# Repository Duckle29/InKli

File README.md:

# InKli

From the Danish "Indeklima" or "indoor climate", is an small sensor box, measuring CO2, temperature and relative humidity.

It displays this on an E-paper display, to allow you to keep an eye on the air in the room you're in.  
Additionally, as it is made with ESPHome, it can also easily connect to a Homeassistant instance, for further home automation and logging.

## History
Quite some time ago I built an air quality monitor, and played around with it. (https://blog.mikkel.cc/posts/airq/) It had PM10 sensors, CO2 sensors and BME680 for TVOC.

I've since had this running, and while it was fine, it was bulky, and I only ever really paid attention to the temperature, humidity and CO2 sensors.
The display I used on that box also had issues. Mainly with the backlight being a significant heat source, and an annoyance at night.

So now this is the replacement.
It has:
- ESP32
- 2.13" Waveshare E-paper display  (https://www.waveshare.com/2.13inch-e-paper.htm)
- IR remote demodulator
- 2 side-firing high-current IR LEDs 
- QWIIC port for future expansion / experimentation
- Single push button
- Touch-pad under screen (tested, works so~so, not great)
It also has a (hopefully) quite efficient 3V3 buck regulator to reduce self heating. (pretty good, seems around 2-3C self heating enclosed, mostly from the ESP itself )

At this point, I have the displays and the sensors. I'm getting most things working first, so I don't learn I've used a strapping pin when I have PCBs in hand and they don't cooperate.
I'm pretty happy with the simple display layout, and will see tomorrow how the graph turns out (set to 8h)

The IR blasters are there because one of these sensors will pull double duty, and act as an IR remote for a heat pump. 
On the rest of the PCBs these probably won't be populated.

## Firmware

There are two variants, both in `esphome/`:

- `inkli.yaml`: the device itself (CO2, temperature and humidity on the e-paper display, Home Assistant, Wi-Fi setup). This is the one for boards without the IR LED fitted.
- `inkli-heatpump.yaml`: the same, plus Panasonic heat pump control over the IR LED. It includes `inkli.yaml` and adds `heatpump.yaml`.

Each release has both: `inkli-esp32.*` and `inkli-heatpump-esp32.*`. A device updates itself (hold the button for 6 s) from the file with its own name on the OTA server.

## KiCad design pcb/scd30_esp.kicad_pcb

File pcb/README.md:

# SCD30 ESP32 backback

This is a small PCB combining an ESP32 WROOM module with an SCD30. It's intended to be USB powered, and has the option to mount a CH340C if you want on-board USB<>serial.

It's intended for use with ESPHome or similar.

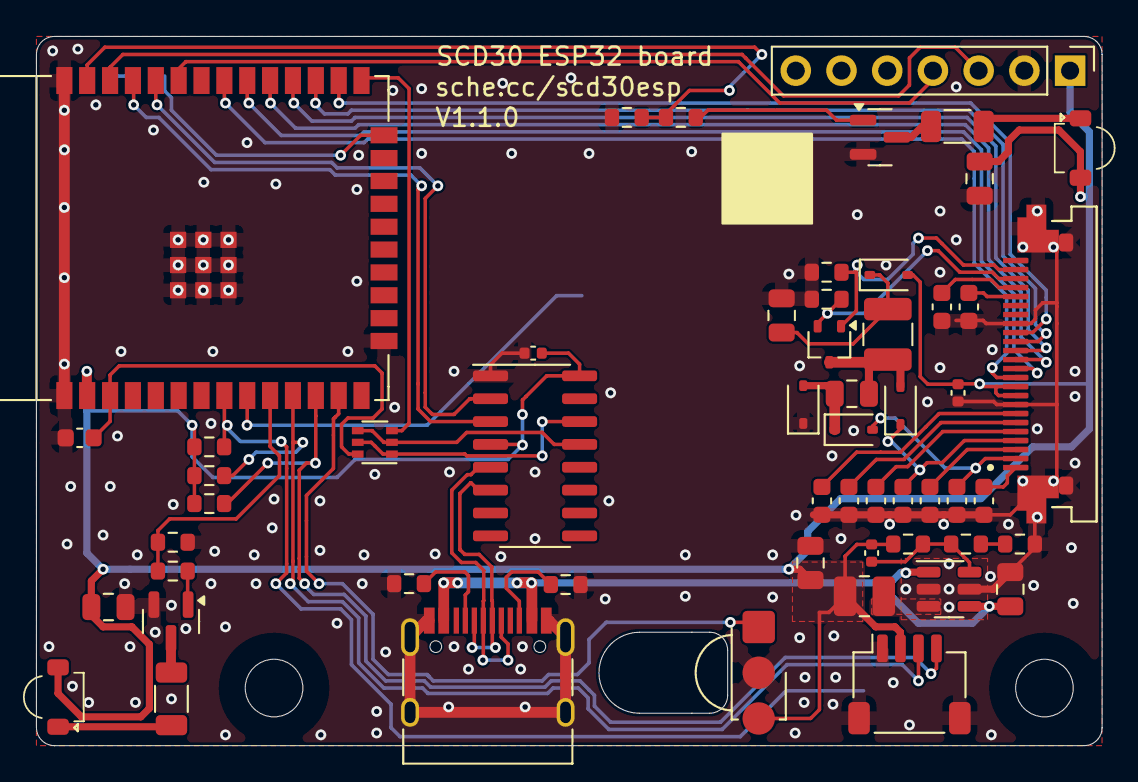
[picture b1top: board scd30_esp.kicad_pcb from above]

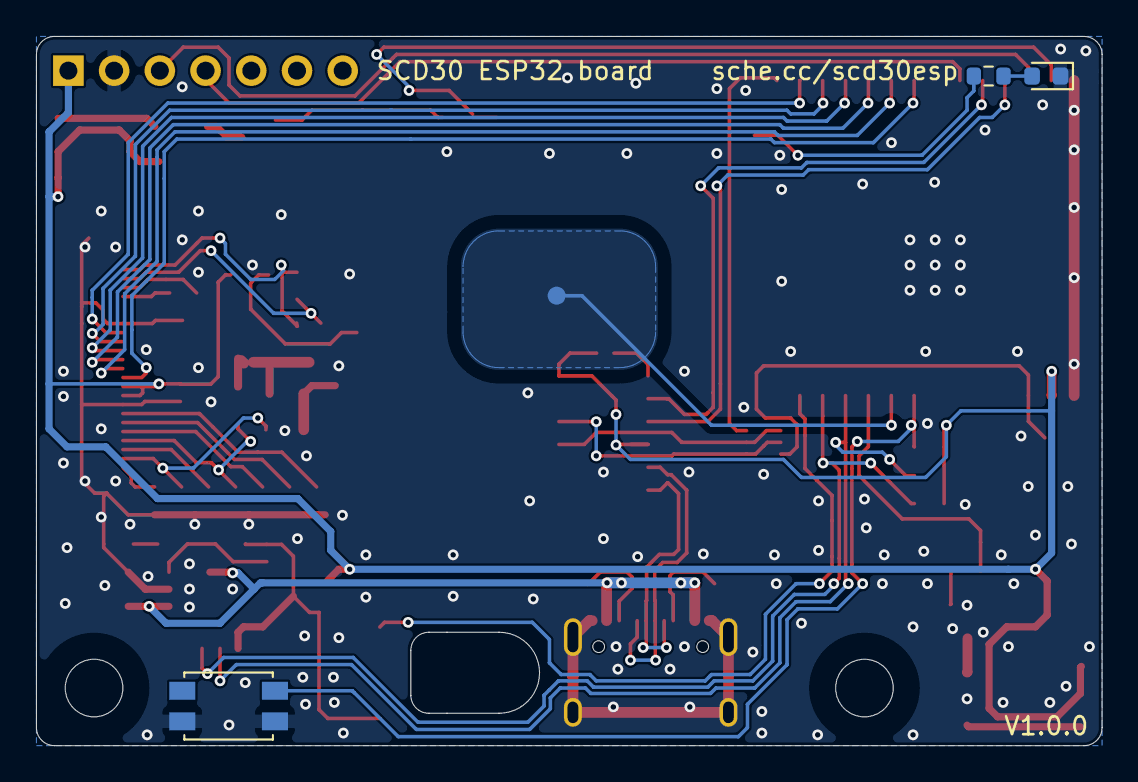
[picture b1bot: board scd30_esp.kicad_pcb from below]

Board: 2 copper layers, 59.2 x 39.4 mm, 59 parts (4 on the bottom side), 53 nets.

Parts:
C1: 120pF; C_0402_1005Metric
C2, C6, C7: 22uF; C_0805_2012Metric
C3: 4.7uF; C_0805_2012Metric
C4, C20: 0.1uF; C_0402_1005Metric
C5, C10, C11, C12, C13, C14, C15, C16, C17, C18: 1uF; C_0603_1608Metric
C8, C9: 4u7; C_0805_2012Metric
D1, D2, D3, D4: NSR0530HT1G; D_SOD-323
D5, D6: LED_Small; LED_Vishay_VSMB2943SL
D7: LED_Small; LED_0603_1608Metric
J1: SCD30; PinHeader_1x07_P2.54mm_Vertical
J2: USB_C_Receptacle_USB2.0; USB_C_Receptacle_HRO_TYPE-C-31-M-12
J3: 24P P0.5mm waveshare E-paper display; AMPHENOL_SFV24R-4STE1HLF
J4: QWIIC; JST_SH_SM04B-SRSS-TB_1x04-1MP_P1.00mm_Horizontal
L1: 1uH; L_1008_2520Metric
L2: 68uF; L_1210_3225Metric
Q1: Si1308EDL; SOT-323_SC-70
Q2, Q4: Q_NMOS_GSD; SOT-23
Q3: BSS138PS; SOT-363_SC-70-6
R1: 82k; R_0603_1608Metric
R2: 8k2; R_0603_1608Metric
R3, R7, R10, R13, R14: 10k; R_0603_1608Metric
R4, R5: 5k1; R_0603_1608Metric
R6: 3R; R_0603_1608Metric
R8, R9, R12, R15: 2k2; R_0603_1608Metric
R11, R16: 3R; R_1206_3216Metric
R17: 1k; R_0603_1608Metric
SW1: SW_SPST; SW_SPST_EVQP2
TP1: Touch TP; TestPoint_Pad_D1.0mm
U1: TPS62A01PDDCR; SOT-23-6
U2: ESP32-WROOM-E; ESP32-WROOM-32E
U3: CH340C; SOIC-16_3.9x9.9mm_P1.27mm
U4: TSOP38G36; Vishay_MINICAST-3Pin

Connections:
+3V3: C1.1, C2.1, C4.1, C6.1, C7.1, C20.1, D1.2 (A), D5.2 (A), D6.2 (A), J1.1, J3.9, J3.10, J4.2, L1.2, R1.1, R8.1, R9.1, R10.1, U2.2 (3V3), U3.4 (V3), U3.16 (VCC), U4.3 (Vs)
/BTN: R10.2, SW1.1 (A), U2.8 (32K_XP/GPIO32/ADC1_CH4)
/D+: J2.A6 (D+), J2.B6 (D+), U3.5 (UD+)
/D-: J2.A7 (D-), J2.B7 (D-), U3.6 (UD-)
/DISP_BUSY: J3.16, U2.26 (ADC2_CH0/GPIO4)
/DISP_SDA: J3.11, U2.31 (GPIO19)
/ESP_EN: C5.1, Q3.6 (D), U2.3 (EN/CHIP_PU)
/ESP_IO0: Q3.3 (D), U2.25 (GPIO0/BOOT/ADC2_CH1)
/IR_RX: U2.13 (MTMS/GPIO14/ADC2_CH6), U4.1 (OUT)
/IR_TX_L: R12.1, R13.1, U2.37 (GPIO23)
/IR_TX_R: R14.1, R15.1, U2.10 (DAC_1/ADC2_CH8/GPIO25)
/MCU_RX+: U2.34 (U0RXD/GPIO3), U3.2 (TXD)
/MCU_TX-: U2.35 (U0TXD/GPIO1), U3.3 (RXD)
/QWIIC_SCL: J4.4, R9.2, U2.12 (ADC2_CH7/GPIO27)
/QWIIC_SDA: J4.3, R8.2, U2.11 (DAC_2/ADC2_CH9/GPIO26)
/SCL: J1.3, U2.36 (GPIO22)
/SCLK: J3.12, U2.30 (GPIO18)
/SDA: J1.4, U2.33 (GPIO21)
/TOUCH: TP1.1 (1_1), U2.9 (32K_XN/GPIO33/ADC1_CH5)
/Waveshare E-ink/GDR: J3.23, Q1.1 (G), R7.1
/Waveshare E-ink/RESE: J3.22, Q1.2 (S), R6.1
/Waveshare E-ink/VCOM: C10.1, J3.1
/Waveshare E-ink/VGH: C13.1, D4.1 (K), J3.4
/Waveshare E-ink/VGL: C11.1, D3.2 (A), J3.2
/Waveshare E-ink/VPP: C15.1, J3.6
/Waveshare E-ink/VSH1: C14.1, J3.5
/Waveshare E-ink/VSH2: C17.1, J3.20
/Waveshare E-ink/VSL: C12.1, J3.3
/Waveshare E-ink/V_CORE: C16.1, J3.7
/status_led: R17.2, U2.24 (ADC2_CH2/GPIO2)
/~DISP_CS: J3.13, U2.29 (GPIO5)
/~DISP_D/C: J3.14, U2.28 (GPIO17)
/~DISP_RST: J3.15, U2.27 (GPIO16)
GND: C2.2, C3.2, C4.2, C5.2, C6.2, C7.2, C9.2, C10.2, C11.2, C12.2, C13.2, C14.2, C15.2, C16.2, C17.2, C18.2, C20.2, D2.1 (K), D7.1 (K), J1.2, J2.A1 (GND), J2.A12 (GND), J2.B1 (GND), J2.B12 (GND), J2.S1 (SHIELD), J3.8, J3.17, J3.MP (MountPin), J4.1, J4.MP (MountPin), Q2.2 (S), Q4.2 (S), R3.2, R4.2, R5.2, R6.2, R7.2, R13.2, R14.2, SW1.2 (B), U1.2 (GND), U1.5 (PG), U2.1 (GND), U2.15 (GND), U2.38 (GND), U2.39 (GND_THERMAL), U3.1 (GND), U4.2 (GND)
unnamed: C9.1, D1.1 (K), L2.1
unnamed: C8.2, D2.2 (A), D3.1 (K)
unnamed: C8.1, D4.2 (A), L2.2, Q1.3 (D)
unnamed: D5.1 (K), R11.1
unnamed: D6.1 (K), R16.1
unnamed: D7.2 (A), R17.1
unnamed: J2.A5 (CC1), R5.1
unnamed: J2.B5 (CC2), R4.1
unnamed: C18.1, J3.21
unnamed: Q2.3 (D), R11.2
unnamed: Q2.1 (G), R12.2
unnamed: Q3.2 (G), Q3.4 (S), U3.13 (~DTR)
unnamed: Q3.1 (S), Q3.5 (G), U3.14 (~RTS)
unnamed: Q4.3 (D), R16.2
unnamed: Q4.1 (G), R15.2
unnamed: R2.2, R3.1
unnamed: C1.2, R1.2, R2.1, U1.6 (FB)
unnamed: L1.1, U1.3 (SW)
VBUS: C3.1, J2.A4 (VBUS), J2.A9 (VBUS), J2.B4 (VBUS), J2.B9 (VBUS), U1.1 (EN), U1.4 (VIN)

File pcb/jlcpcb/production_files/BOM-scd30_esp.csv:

Comment,Designator,Footprint,LCSC,Quantity
120pF,C1,C_0402_1005Metric,C106996,1
0.1uF,"C20,C4",C_0402_1005Metric,C1525,2
1uF,"C10,C11,C12,C13,C14,C15,C16,C17,C5,C8,C9",C_0603_1608Metric,C15849,11
USB_C_Receptacle_USB2.0,J2,USB_C_Receptacle_HRO_TYPE-C-31-M-12,C165948,1
BSS138PS,Q3,SOT-363_SC-70-6,C193381,1
4.7uF,C3,C_0805_2012Metric,C19666,1
68uF,L2,L_1210_3225Metric,C223228,1
TPS62A01PDDCR,U1,SOT-23-6,C22445521,1
LED_Small,D7,LED_0603_1608Metric,C2286,1
360k,R2,R_0603_1608Metric,C23146,1
82k,R1,R_0603_1608Metric,C23254,1
10k,"R10,R13,R14,R17,R3,R7",R_0603_1608Metric,C25804,6
1uH,L1,L_1008_2520Metric,C435392,1
22uF,"C2,C6,C7",C_0805_2012Metric,C45783,3
Si1308EDL,Q1,SOT-323_SC-70,C469327,1
SW_SPST,SW1,SW_SPST_EVQP2,C512395,1
24P P0.5mm waveshare E-paper display,J3,AMPHENOL_SFV24R-4STE1HLF,C5343283,1
NSR0530HT1G,"D1,D2,D3,D4",D_SOD-323,C556393,4
2k2,"R12,R15,R4,R5,R8,R9",R_0603_1608Metric,C6119849,6
ESP32-WROOM-E,U2,ESP32-WROOM-32E,C701342,1
CH340C,U3,SOIC-16_3.9x9.9mm_P1.27mm,C7464026,1
3R,R6,R_0603_1608Metric,,1
TSOP38G36,U4,Vishay_MINICAST-3Pin,,1

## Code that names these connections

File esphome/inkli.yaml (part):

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  - platform: gpio
    id: btn
    pin:
      number: GPIO32
      inverted: True
      #allow_other_uses: True
      mode:
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                - display.page.show: page_co2_graph

  # - platform: esp32_touch
  #   pin: GPIO33
  #   threshold: 1040
  #   id: touch_test
  #   filters:
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output:
  - platform: ledc
    id: led_status
    pin: GPIO2
    frequency: 19531

# On epaper_spi the old COLOR_ON / COLOR_OFF constants mean white / black ink (the reverse of waveshare_epaper),
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  - platform: epaper_spi
    id: disp
    model: waveshare-2.13in-v3
    cs_pin: GPIO5
    dc_pin: GPIO17
    reset_pin: GPIO16
    busy_pin: GPIO4
    data_rate: 2MHz  # what the old driver ran at
    full_update_every: 60
    rotation: 270
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    type: std::function<void(esphome::display::Display &)>

spi:
  clk_pin: GPIO18
  mosi_pin: GPIO19

i2c:
  - id: i2c_scd30
    sda: GPIO21
    scl: GPIO22
    scan: False
  
  - id: qwiic
    sda: GPIO26
    scl: GPIO27
    scan: True

http_request:
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
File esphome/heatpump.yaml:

# Heat pump add-on for InKli: Panasonic IR control, a "Heat pump" climate entity and a vane position select.
# Not a standalone config. inkli-heatpump.yaml combines it with inkli.yaml.
# It relies on the SCD30 sensors (scd30_t, scd30_rh) defined there.

# IR. Only the left LED (IR_TX_L, GPIO23) is populated on this board for now;
# the right one is IR_TX_R on GPIO25.
remote_transmitter:
  pin: GPIO23
  carrier_duty_percent: 50%

remote_receiver:
  id: rcvr
  pin:
    number: GPIO14  # TSOP38G36 output is active low
    inverted: true
    mode:
      input: true
      pullup: true
  # A Panasonic AC frame is 220 symbols; the default of 192 is too small and
  # the frame would be dropped. 256 is the ESP32 value from the ESPHome docs.
  rmt_symbols: 256
  receive_symbols: 256

climate:
  - platform: panasonic_ir
    id: heat_pump
    name: "Heat pump"
    model: PKE
    receiver_id: rcvr
    sensor: scd30_t
    humidity_sensor: scd30_rh

select:
  # The component's own vane select offers "Auto" and "1" to "5" (1 = highest). It is kept
  # (hidden) as the thing that talks to the heat pump, and the friendly one below sits on top.
  # Both lists have the same order, so the index maps straight across.
  - platform: panasonic_ir
    panasonic_ir_id: heat_pump
    vane_position:
      id: vane_raw
      internal: true
      # Follows the vane when the original remote (or a mode change) moves it
      on_value:
        - lambda: id(vane_pos).publish_state(i);

  - platform: template
    id: vane_pos
    name: "Heat pump vane position"
    icon: "mdi:arrow-expand-vertical"
    options:
      - Auto
      - Highest
      - High
      - Middle
      - Low
      - Lowest
    optimistic: false
    set_action:
      # Only the chosen name (x) is available here, so look up its position. Same order as the
      # options above and as the component's own select, so the position is also its index there.
      - select.set_index:
          id: vane_raw
          index: !lambda |-
            static const char *const names[] = {"Auto", "Highest", "High", "Middle", "Low", "Lowest"};
            for (size_t n = 0; n < 6; n++) {
              if (x == names[n]) return n;
            }
            return (size_t) 0;

esphome:
  on_boot:
    # The template select has no state until something publishes one, so copy it over once at boot
    - priority: -100
      then:
        - lambda: |-
            auto idx = id(vane_raw).active_index();
            if (idx.has_value()) id(vane_pos).publish_state(*idx);

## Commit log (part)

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2024-12-28 Saved schematic
2025-01-01 Initial schematic
2025-01-03 Initial layout
2025-01-17 moved files to sub-folders
2025-01-17 readme
2025-01-23 Added alternate footprint for XFCN FPC connector
2025-01-23 nudged components, added version text
2025-01-23 Added JLCPCB production files
2025-02-15 Initial esphome yaml, and 3D CAD
2025-02-15 Commented out min_version for now
2025-02-15 Added factory reset
2025-02-15 unbumped version
2025-02-15 Dedupe button
2025-02-16 Updated hosing design. Name change to InKli
2025-02-16 Added setup instructions
2025-02-16 Update case clearances slightly
2025-02-19 Set min ESPHome version to 2025.02.00
2025-02-19 Added actions for CI and publishing
2025-02-19 remove double file extension
2025-02-19 no .factory yaml
2025-02-19 Updated workflow actions to v4
2025-02-19 change publish workflow trigger
2025-03-04 Add wifi info to main screen, and disable wifi if unconnected for >5min
2025-03-29 Added image to readme
2025-04-20 Updated CAD files for better printability
2025-04-20 Don't do CI for now
2025-04-20 use latest esphome for builds
2025-04-20 Trigger workflow on release trigger
2025-04-20 no ci
2025-04-20 Version bump
2025-04-20 Work on http ota
2025-04-21 Version bump to test webhook
2025-04-21 Initial work on pushing files to ota server over SCP
2025-04-21 version bump for test
2025-04-21 fix string, depend on upload job
2025-04-21 Upload files to proper subdir
2025-04-21 Got http ota working
2025-04-21 Remove touch
2025-04-21 Cherrypicked wifi info commit
2025-04-27 Do a display update when triggering a new display page
